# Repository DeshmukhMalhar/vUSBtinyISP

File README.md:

# vUSBtinyISP
USB ISP programmer using attiny85 for AVR
This repo contains the eagle schematics and board,Which can be constructed on a prefbord.

The usbtiny.hex file is to be flashed on the t85.
This works on t45,t85. 
The "what should happen" tells you the output of avrdude andl lists the commands required
If you find any issues, please report.

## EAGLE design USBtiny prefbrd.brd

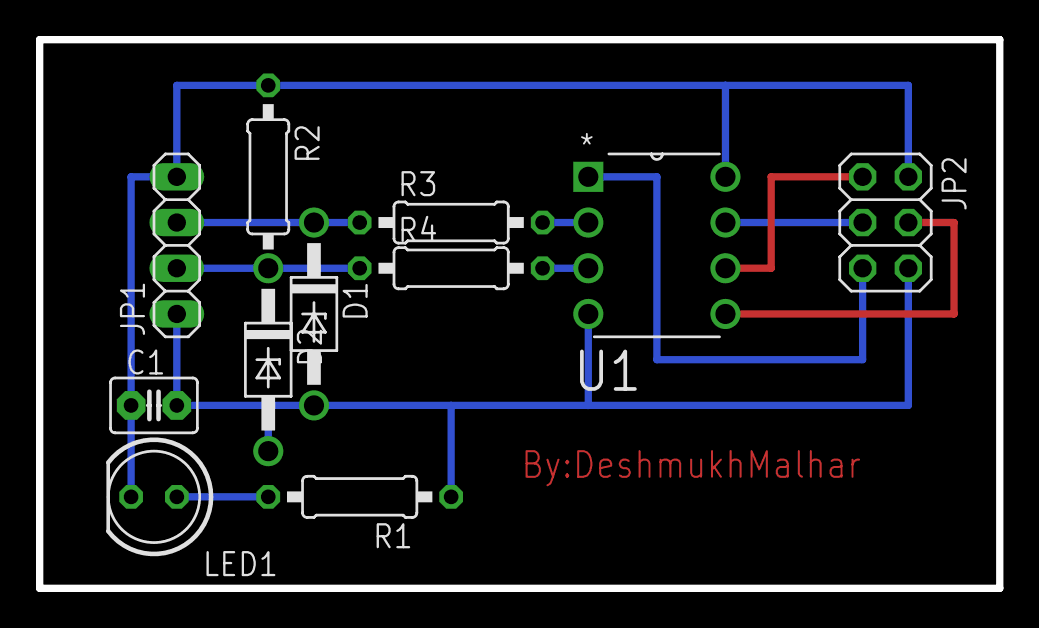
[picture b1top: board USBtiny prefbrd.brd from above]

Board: 2 copper layers, 53.3 x 30.5 mm, 11 parts (0 on the bottom side), 11 nets.

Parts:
C1: C2.5-3
D1, D2: DO41Z10
JP1: C1; 1X04
JP2: C2; 2X03
LED1: LED5MM
R1: 100; 0207/10
R2: 1K7; 0207/10
R3, R4: 68R; 0207/10
U1: ATTINY85-20PU; DIP254P762X533-8

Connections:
+5V: C1.1, JP1.4, JP2.2, LED1.K, R2.1, U1.8
GND: C1.2, D1.A, D2.A, JP1.1, JP2.6, R1.1, U1.4
unnamed: R3.2, U1.2
unnamed: R4.2, U1.3
unnamed: D2.C, JP1.2, R2.2, R4.1
unnamed: D1.C, JP1.3, R3.1
unnamed: JP2.5, U1.1
unnamed: JP2.1, U1.6
unnamed: JP2.3, U1.7
unnamed: JP2.4, U1.5
unnamed: LED1.A, R1.2

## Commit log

2016-03-29 Added files via upload
